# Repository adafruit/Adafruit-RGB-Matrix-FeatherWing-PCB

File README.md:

## Adafruit RGB Matrix Featherwing Kit PCB - For M0 and M4 Feathers
<br/>
<a href="http://www.adafruit.com/products/3036"><br/>
Click here to purchase one from the Adafruit shop</a>

PCB files for the Adafruit RGB Matrix Featherwing Kit. Format is EagleCAD schematic and board layout
* https://www.adafruit.com/product/3036

### Description

Ahoy! It's time to create a dazzling light up project with our new RGB Matrix FeatherWing. Now you can quickly and easily create projects featuring your favorite 16 or 32-pixel tall matrix boards. Using our RGB Matrix library is easy and works wonderfully with any of our M0, M4 or nRF52840 Feathers.

Please note: This wing is only tested/designed to work with the SAMD21 M0, SAMD51 M4 and nRF52840 Feathers. It's not for use with any other Feathers at this time. (That said, if you'd like to add support, [we'd be happy to take a pull request](https://github.com/adafruit/RGB-matrix-Panel) on the library repo)

This wing can be assembled in one of two ways. You can either solder in a 2x8 IDC shrouded header on the top, then plug in the IDC cable that came with your matrix. This makes it easy to stack on top of your Feather. Or, you can solder in the 2x10 socket header on the bottom of the Wing, and then stack your Feather on top. That way you can plug it directly into the back of the matrix *mind blown*

This FeatherWing will work great with any of our [16x32](https://www.adafruit.com/?q=16x32), [32x32](https://www.adafruit.com/?q=32x32) or [64x32](https://www.adafruit.com/?q=64x32) RGB matrices, and is definitely the easiest way to glow and go.

Either way you decide to go, you can plug a 5V DC power pack into the 2.1mm DC jack. That 5V is polarity protected and then output on the other side to a 5.08mm terminal block. An onboard regulator will provide 3.3V power to your Feather so you don't need a separate USB or battery, this makes for a very compact build!

### License

Adafruit invests time and resources providing this open source design, please support Adafruit and open-source hardware by purchasing products from [Adafruit](https://www.adafruit.com)!

Designed by Limor Fried/Ladyada for Adafruit Industries.

Creative Commons Attribution/Share-Alike, all text above must be included in any redistribution. See license.txt for additional details.

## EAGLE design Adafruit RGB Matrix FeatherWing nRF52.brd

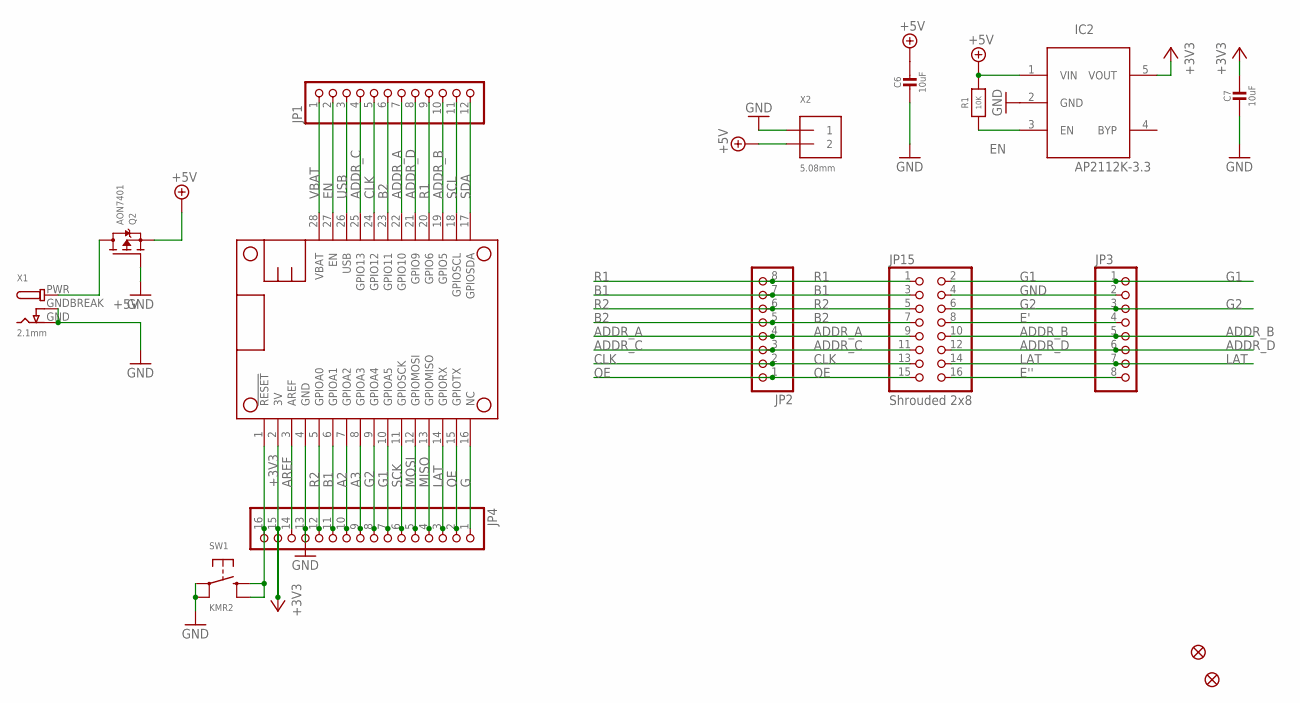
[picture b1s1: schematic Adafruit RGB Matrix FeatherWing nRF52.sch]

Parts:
C6, C7: 10uF; 0805-NO
FID1, FID3: FIDUCIAL_1MM
IC2: AP2112K-3.3; SOT23-5L
JP1: HEADER-1X12; 1X12_ROUND
JP2, JP3: HEADER-1X870MIL; 1X08_ROUND_70
JP4: HEADER-1X16ROUND; 1X16_ROUND
JP15: Shrouded 2x8; 2X08_SHROUDED
MS1: FEATHERWING
Q2: AON7401; POWERDI3333
R1: 10K; 0603-NO
SW1: KMR2; BTN_KMR2_4.6X2.8
X1: 2.1mm; DCJACK_2MM_PTH
X2: 5.08mm; TERMBLOCK_508_1X2

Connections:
+3V3: C7.1, IC2.5 (VOUT), JP4.15, MS1.2 (3V)
+5V: C6.1, IC2.1 (VIN), Q2.1 (S), Q2.2 (S), Q2.3 (S), R1.2, X2.P$4 (2)
A2: JP4.10, MS1.7 (GPIOA2)
A3: JP4.9, MS1.8 (GPIOA3)
ADDR_A: JP1.7, JP2.4, JP15.9, MS1.22 (GPIO10)
ADDR_B: JP1.10, JP3.5, JP15.10, MS1.19 (GPIO5)
ADDR_C: JP1.4, JP2.3, JP15.11, MS1.25 (GPIO13)
ADDR_D: JP1.8, JP3.6, JP15.12, MS1.21 (GPIO9)
AREF: JP4.14, MS1.3 (AREF)
B1: JP2.7, JP4.11, JP15.3, MS1.6 (GPIOA1)
B2: JP1.6, JP2.5, JP15.7, MS1.23 (GPIO11)
CLK: JP1.5, JP2.2, JP15.13, MS1.24 (GPIO12)
E': JP3.4, JP15.8
E'': JP3.8, JP15.16
EN: IC2.3 (EN), JP1.2, MS1.27 (EN), R1.1
G: JP4.1, MS1.16 (NC)
G1: JP3.1, JP4.7, JP15.2, MS1.10 (GPIOA5)
G2: JP3.3, JP4.8, JP15.6, MS1.9 (GPIOA4)
GND: C6.2, C7.2, IC2.2 (GND), JP3.2, JP4.13, JP15.4, MS1.4 (GND), Q2.4 (G), SW1.A, SW1.A' (P1), X1.GND, X1.GNDBREAK, X2.P$3 (1)
LAT: JP3.7, JP4.3, JP15.14, MS1.14 (GPIORX)
MISO: JP4.4, MS1.13 (GPIOMISO)
MOSI: JP4.5, MS1.12 (GPIOMOSI)
OE: JP2.1, JP4.2, JP15.15, MS1.15 (GPIOTX)
R1: JP1.9, JP2.8, JP15.1, MS1.20 (GPIO6)
R2: JP2.6, JP4.12, JP15.5, MS1.5 (GPIOA0)
RESET: JP4.16, MS1.1 (!RESET), SW1.B (S), SW1.B' (S1)
SCK: JP4.6, MS1.11 (GPIOSCK)
SCL: JP1.11, MS1.18 (GPIOSCL)
SDA: JP1.12, MS1.17 (GPIOSDA)
USB: JP1.3, MS1.26 (USB)
VBAT: JP1.1, MS1.28 (VBAT)
VIN: Q2.5678 (D), X1.PWR

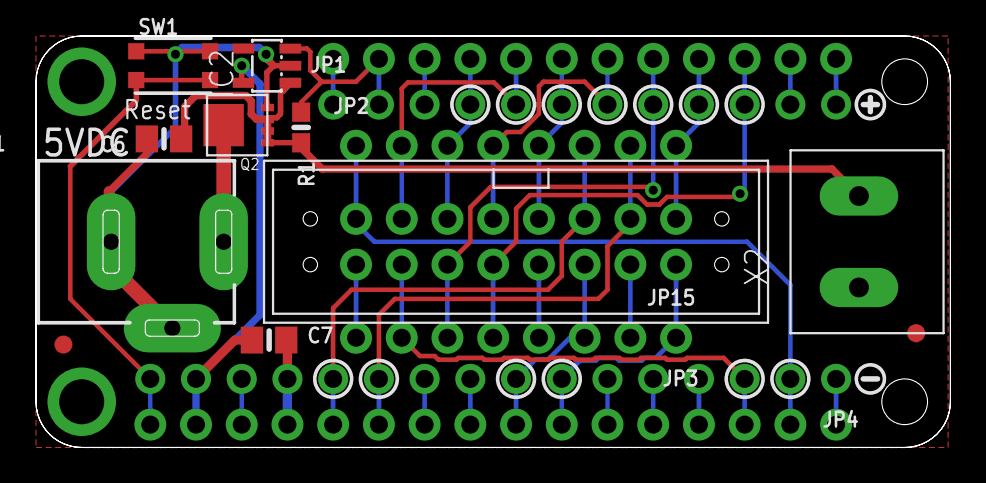
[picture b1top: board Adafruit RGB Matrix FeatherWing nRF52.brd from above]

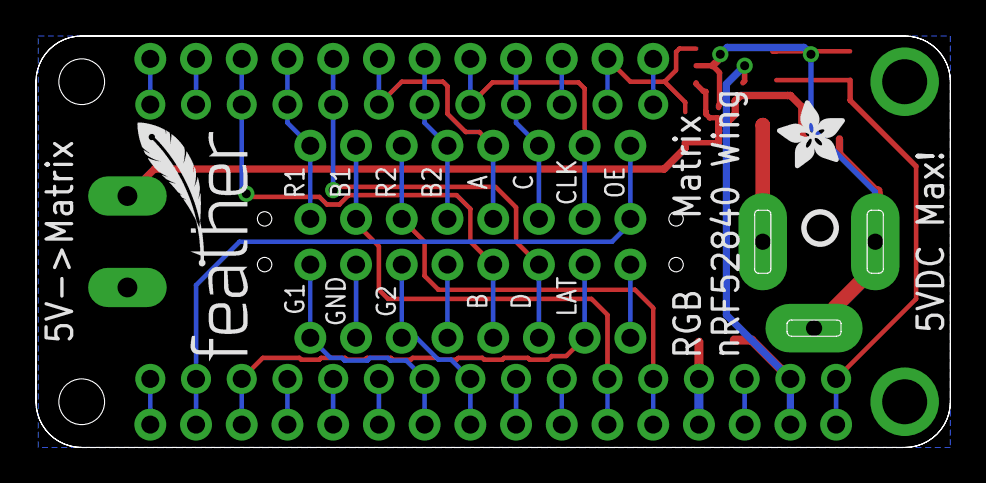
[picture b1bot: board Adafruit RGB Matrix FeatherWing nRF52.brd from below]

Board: 2 copper layers, 50.8 x 22.9 mm, 21 parts (3 on the bottom side), 32 nets.

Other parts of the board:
U$1: SYMBOL_PLUS
U$2: PCBFEAT-REV-040
U$3: FEATHERLOGO_SMALL
U$6: SYMBOL_MINUS
U$7: ADAFRUIT_3.5MM

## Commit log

2018-08-22 init
2019-07-16 updating to use pcb page cookiecutter
2020-08-21 Add nRF board files.
2020-08-21 Add nRF image
